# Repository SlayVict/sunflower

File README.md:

# Sunflower

Corne like keyboard I made to tinker with ergogen. Case model is not ready to share

## Components

- khail choc brown
- nice! nano v2
- Li POI 301230 batteries
- batteries connector I honestly don't know the name of
- Reset Switch SPID 4-pin Flat
- Power Switch - Micro SMD SPOT
- khail choc hotswap sockets

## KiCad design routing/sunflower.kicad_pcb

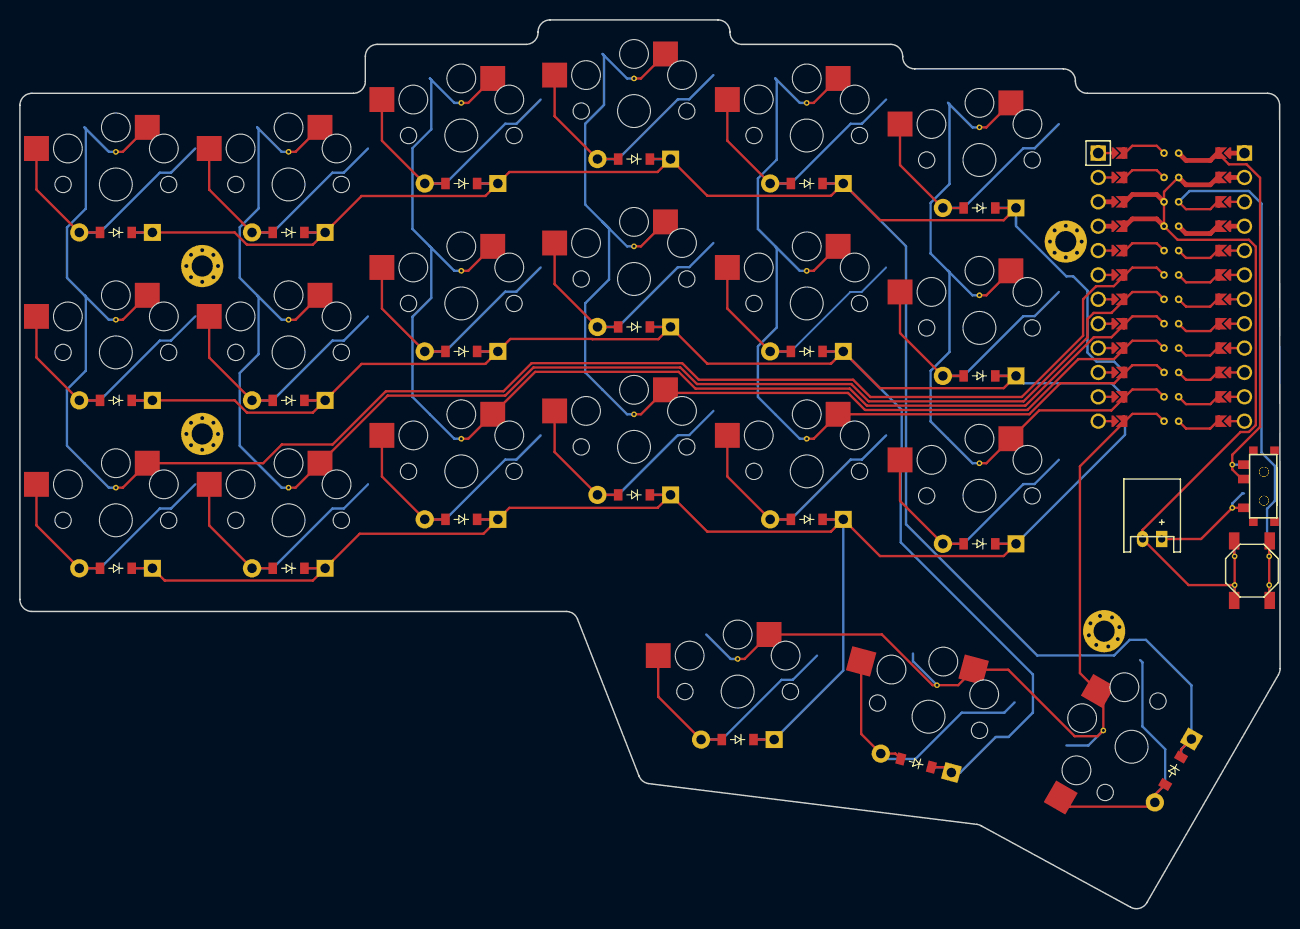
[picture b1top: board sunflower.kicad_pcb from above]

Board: 2 copper layers, 131.3 x 92.6 mm, 52 parts (0 on the bottom side), 34 nets.

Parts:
B1, B2: SW_TACT_ALPS_SKQGABE010
D1, D2, D3, D4, D5, D6, D7, D8, D9, D10, D11, D12, D13, D14, D15, D16, D17, D18, D19, D20, D21: ComboDiode
JST1: JST_PH_S2B-PH-K_02x2.00mm_Angled
MCU1: ProMicro
S1, S2, S3, S4, S5, S6, S7, S8, S9, S10, S11, S12, S13, S14, S15, S16, S17, S18, S19, S20, S21: PG1350
T1, T2: SPDT_C128955
_28, _29, _30, _31: MountingHole_2.2mm_M2_Pad_Via

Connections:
GND: B1.1, B2.1, JST1.2, MCU1.2, MCU1.21, MCU1.22
P3: MCU1.19, S1.1, S2.1, S3.1
P4: MCU1.18, S4.1, S5.1, S6.1
P5: MCU1.17, S7.1, S8.1, S9.1
P6: MCU1.16, S10.1, S11.1, S12.1
P7: MCU1.15, S13.1, S14.1, S15.1
P8: MCU1.14, S16.1, S17.1, S18.1
P9: MCU1.13, S19.1, S20.1, S21.1
P10: D1.1, D4.1, D7.1, D10.1, D13.1, D16.1, D19.1, MCU1.12
P14: D3.1, D6.1, D9.1, D12.1, D15.1, D18.1, D21.1, MCU1.10
P16: D2.1, D5.1, D8.1, D11.1, D14.1, D17.1, D20.1, MCU1.11
RAW: JST1.1, MCU1.1, T1.1, T1.2, T2.1, T2.2
RST: B1.2, B2.2, MCU1.3
cozy_default: D19.2, S19.2
index_bottom: D13.2, S13.2
index_home: D14.2, S14.2
index_top: D15.2, S15.2
inner_bottom: D16.2, S16.2
inner_home: D17.2, S17.2
inner_top: D18.2, S18.2
middle_bottom: D10.2, S10.2
middle_home: D11.2, S11.2
middle_top: D12.2, S12.2
pinky2_bottom: D4.2, S4.2
pinky2_home: D5.2, S5.2
pinky2_top: D6.2, S6.2
pinky_bottom: D1.2, S1.2
pinky_home: D2.2, S2.2
pinky_top: D3.2, S3.2
reachy_default: D21.2, S21.2
ring_bottom: D7.2, S7.2
ring_home: D8.2, S8.2
ring_top: D9.2, S9.2
tucky_default: D20.2, S20.2

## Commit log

2024-02-17 updated promicro_pretty to work
2024-05-02 final version
2024-05-02 routing
2024-06-02 hehe
2025-05-20 update to gitignore
2025-05-20 remove extra footprints
2025-05-20 updated config to create dxf with mounting holes for future use in fusion
2025-05-20 fixed routing for F (qwerty) key
2025-05-20 remove accidentally saved file
2025-06-06 remove useless files
